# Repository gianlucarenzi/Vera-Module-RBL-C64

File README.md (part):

# VERA Module RBL-C64

<div align="center">

*🌐 English | [🌐 Italiano](#vera-module-rbl-c64-italiano)*

</div>

> [!WARNING]
> **v1.0 — PRE-PRODUCTION.**
> The PCB is routed and passes KiCad's DRC; the first boards are being made and are **not tested
> yet**. Firmware (ESP32, FPGA) and documentation have only been checked in simulation or on
> paper and may contain errors.

<div align="center">

**Commander X16 graphics and sound for the Commodore 64, through the expansion port.**

*▶ Teaser: 32 s with sound (Ctrl+click to open it in a new tab)*

</div>

## 🎮 What it can look like

What a game can look like on the VERA (320×240, 256 colours). These are **illustrative mock-ups
of two original demo games, not captures from the board**; `tools/make_demo_shots.py` draws them.

<div align="center">

*IRONHOLD (side-scrolling action) and CIRCUIT RUNNER (maze chase)*
</div>

## 📦 v1.0 — pre-production

- **USB:** CH340C USB-serial (internal clock, no crystal) on USB-C, with ESP32 auto-reset.
- **U11 WM8524** (C146242) is short at JLCPCB: it is in `jlcpcb-global-sourcing.txt`; choose
  **Global Sourcing** for that row when ordering.
- The BOM XML comes straight from the KiCad 5 schematic (`utilities/kicadcli`), which stops on
  parts without annotation; `./output_job.sh 1.0` makes the JLCPCB files.

---

<div style="background: #ffffff; border-radius: 16px; padding: 24px; margin: 24px 0; box-shadow: 0 4px 12px rgba(0,0,0,0.1); border: 1px solid #e0e0e0;">

## 📋 Table of Contents

- [🔍 Overview](#-overview)
- [✨ Features](#-features)
- [⚙️ Technical Specifications](#️-technical-specifications)
- [🔧 Hardware Components](#-hardware-components)
- [🖼️ Board Preview](#️-board-preview)
- [📐 PCB Layers](#-pcb-layers)
- [🔌 Connectors & Interfaces](#-connectors--interfaces)
- [⚡ Power Requirements](#-power-requirements)
- [🔨 Assembly Instructions](#-assembly-instructions)
- [📦 Bill of Materials](#-bill-of-materials)
- [💻 Programming & Configuration](#-programming--configuration)
- [📁 Project Structure](#-project-structure)
- [🤝 Contributing](#-contributing)
- [📄 License](#-license)

</div>

---

<div style="background: #ffffff; border-radius: 16px; padding: 24px; margin: 24px 0; box-shadow: 0 4px 12px rgba(0,0,0,0.1); border: 1px solid #e0e0e0;">

## 🔍 Overview

The **VERA Module RBL-C64** is an FPGA-based audio and video expansion card for the
**Commodore 64**. It plugs into the **expansion (cartridge) port** and adds, in the I/O
areas `IO1`/`IO2`, the VERA registers and a **256 KB GeoRAM** emulated by the ESP32.

### What is VERA?

**VERA** (Video Enhanced Retro Adapter) is originally designed for the 
Commander X16 computer, whose 65C02 bus is close to the 6510 one. It provides:

- **Advanced Graphics**: Multiple video layers, sprites, and high-resolution modes
- **Enhanced Audio**: Multi-channel digital audio with PCM and PSG capabilities  
- **Modern Connectivity**: VGA output, SD card storage, and USB programming
- **Retro Compatibility**: Integration with C64 software through a small register map

</div>

---

<div style="background: #ffffff; border-radius: 16px; padding: 24px; margin: 24px 0; box-shadow: 0 4px 12px rgba(0,0,0,0.1); border: 1px solid #e0e0e0;">

## ✨ Features

### 🎨 Graphics Capabilities

#### Video Output
- **VGA Output**: 640x480 @ 60Hz with analog RGB signals
- **Multiple Layers**: Background, foreground, and sprite layers
- **Color Depth**: 256 colors from a palette of 4096
- **Sprites**: Hardware-accelerated sprite engine
- **Scrolling**: Smooth horizontal and vertical scrolling

#### Audio Features
- **Digital Audio**: High-quality PCM audio output
- **Multi-channel**: Stereo audio
- **Audio Codec**: WM8524 for professional audio quality
- **3.5mm Jack**: Standard audio output connector

### 🔗 System Integration

#### Commodore 64 Compatibility
- **Expansion Port**: Direct connection to the C64 cartridge port, no ROM mapping (`/GAME`, `/EXROM` unused)
- **I/O Mapping**: VERA registers at `$DF00–$DF1F`, select latch at `$DFFD`, GeoRAM window at `$DE00–$DEFF` with page/block registers at `$DFFE`/`$DFFF`
- **GeoRAM 256 KB**: emulated in the ESP32 RAM, register compatible with the original cartridge
- **Bus Decoder**: cycles qualified by the C64 `/IO1` and `/IO2` lines (CPU accesses only, VIC-II fetches ignored); A0–A7 give the offset
- **Power Management**: Efficient 5V to 3.3V/1.2V conversion

#### Storage & Programming
- **SD Card Slot**: Micro SD for data storage and ROM loading
- **SPI Flash**: 16Mbit W25Q16 for FPGA configuration
- **USB Programming**: CH340C USB-to-serial on USB-C, with ESP32 auto-reset
- **SPI**: Direct FPGA programming interface

</div>

---

<div style="background: #ffffff; border-radius: 16px; padding: 24px; margin: 24px 0; box-shadow: 0 4px 12px rgba(0,0,0,0.1); border: 1px solid #e0e0e0;">

## ⚙️ Technical Specifications

### Core Specifications

| Component | Specification |
|-----------|---------------|
| **FPGA** | Lattice ICE40UP5K-SG48ITR |
| **Microcontroller** | ESP32-S3FN8 |
| **Flash Memory** | W25Q16JVSNIQ (16Mbit) |
| **Audio Codec** | WM8524CGEDT |
| **USB Interface** | CH340C (internal clock, no crystal) |
| **Power Regulators** | AMS1117-3.3V, AMS1117-1.2V, L7805 |
| **Crystal (VERA board)** | 25 MHz ECS-2033-250-BN (ICE40UP5K reference clock) |
| **Crystal (ESP32-S3)** | 40 MHz external — required; XTAL\_P (QFN56 pin 54) / XTAL\_N (pin 53) |
| **PCB Layers** | 4-layer (Signal/Power/GND/Signal) |
| **Board Size** | TBD mm x TBD mm |

### Electrical Characteristics

| Parameter | Min | Typ | Max | Unit |
|-----------|-----|-----|-----|------|
| **Supply Voltage** | 4.5 | 5.0 | 5.5 | V |
| **Current Consumption** | - | 800 | 1200 | mA |
| **Operating Temperature** | -10 | 25 | 70 | °C |
| **VGA Output Impedance** | - | 75 | - | Ω |
| **Audio Output Level** | - | 2.0 | - | Vrms |

</div>

---

<div style="background: #ffffff; border-radius: 16px; padding: 24px; margin: 24px 0; box-shadow: 0 4px 12px rgba(0,0,0,0.1); border: 1px solid #e0e0e0;">

## 🔧 Hardware Components

### Main Processing Units

#### FPGA - ICE40UP5K
- **Logic Elements**: 5,280 LUTs
- **Memory**: 120 Kbit BRAM, 1 Mbit SPRAM
- **I/O Pins**: 39 user I/O
- **Package**: QFN-48 (7x7mm)
- **Programming**: SPI configuration

#### ESP32-S3FN8
- **CPU**: Dual-core Xtensa LX7 @ 240 MHz
- **Memory**: 8 MB in-package Quad SPI flash, 512 KB SRAM
- **Connectivity**: Wi-Fi 802.11 b/g/n, Bluetooth 5 LE
- **GPIO**: 45 total (38 usable), all bidirectional
- **Package**: QFN-56 (7×7 mm)
- **Crystal**: requires an external **40 MHz crystal** on dedicated analog pins XTAL\_P (QFN56 pin 54) and XTAL\_N (pin 53) — mandatory for PLL startup; see PIN-MAPPING.md § 5
- **Role**: software 6510-bus controller — qualifies every cycle with `/IO1`/`/IO2`, reads A0–A7, R/W and D0–D7, drives `DEV_SEL_N` for the VERA registers and the data bus for GeoRAM reads; emulates the 256 KB GeoRAM in its internal RAM
- **Timing**: bus loop alone on Core 1 with interrupts masked (Core 0 prints the log on Serial); PHI2, R/W, `/IO1`, `/IO2` and `DEV_SEL_N` through **Dedicated GPIO** Xtensa TIE instructions (`ee.get_gpio_in` / `ee.wr_mask_gpio_out`, 1 CPU cycle) within the ~490 ns PHI2-high window of the ~1 MHz 6510 clock

### Interface Components

#### Audio System
- **Codec**: WM8524CGEDT (24-bit, 192kHz)
- **Interface**: From FPGA digital audio bus
- **Output**: 3.5mm stereo jack
- **SNR**: >100dB

#### Video System
- **Output**: 15-pin VGA connector
- **Resolution**: 640x480 @ 60Hz
- **Colors**: 8-bit RGB (256 colors)
- **Sync**: Separate H/V sync signals

</div>

---

<div style="background: #ffffff; border-radius: 16px; padding: 24px; margin: 24px 0; box-shadow: 0 4px 12px rgba(0,0,0,0.1); border: 1px solid #e0e0e0;">

## 🖼️ Board Preview

### 3D Renderings

#### Top View

*Top side showing main components and connectors*

#### Bottom View  

*Bottom side with additional components*

### Board Dimensions

- **Length**: TBD mm
- **Width**: TBD mm  
- **Thickness**: 1.6mm (4-layer PCB)
- **Mounting**: Commodore 64 expansion port (2×22 edge contacts, 2.54 mm pitch)
- **Connectors**: Flat for space efficiency. It needs a custom 3D printed case

</div>

---

<div style="background: #ffffff; border-radius: 16px; padding: 24px; margin: 24px 0; box-shadow: 0 4px 12px rgba(0,0,0,0.1); border: 1px solid #e0e0e0;">

## 📐 PCB Layers

### Layer Stack-up

#### Layer 1 - Top Copper (F.Cu)

*Component placement and signal routing*

#### Layer 2 - Power Plane (POWER)

*5V, 3.3V, and 1.2V power distribution*

#### Layer 3 - Ground Plane (GND)

*Solid ground plane for signal integrity*

#### Layer 4 - Bottom Copper (B.Cu)

*Additional signal routing and components*

</div>

---

<div style="background: #ffffff; border-radius: 16px; padding: 24px; margin: 24px 0; box-shadow: 0 4px 12px rgba(0,0,0,0.1); border: 1px solid #e0e0e0;">

## 🔌 Connectors & Interfaces

### External Connections

#### Commodore 64 Expansion Port
- **Connector**: expansion (cartridge) port, 2×22 edge contacts, 2.54 mm pitch
- **Address Range**: `IO1` $DE00–$DEFF, `IO2` $DF00–$DFFF
- **Signals used**: D0–D7, A0–A15, PHI2, R/W, `/IO1`, `/IO2`, `/RESET`, `/IRQ`; `BA` and `/DMA` only to test points
- **Unused lines**: `/GAME`, `/EXROM`, `/ROML`, `/ROMH`, `/NMI`, Dot Clock — left unconnected
- **Outputs**: `/IRQ` and `/RESET` through the open-drain buffers `U26` and `U27` (SN74LVC1G07): the board only pulls the shared lines low
- **No audio input** on the expansion port: the VERA audio mix is on test point `TP5`

#### Video Output (J2)
| Pin | Signal | Description |
|-----|--------|-------------|
| 1-3 | RGB | Red, Green, Blue analog signals |
| 13-14 | H/V Sync | Horizontal/Vertical sync |
| 6-10 | GND | Ground connections |
| 11-12 | Audio L/R | Stereo audio output |

#### Storage Interfaces
- **SD Card Slot (J3)**: Micro SD card interface
- **SPI Flash**: On-board 16Mbit storage
- **USB Port (J4)**: Programming and data transfer

### Programming Interfaces

#### ICEPROG Connector (J6)
| Pin | Signal | Function |
|-----|--------|----------|
| 1 | 5V | Power supply |
| 2 | FPGA_CDONE/PULL-UP | FPGA Programmed |
| 3 | FPGA_RESET | FPGA Reset |
| 4 | MISO | SPI data in |
| 5 | MOSI | SPI data out |
| 6 | SCK | SPI clock |
| 7 | SS | SPI select |
| 8 | GND | Ground |

#### Reset & Control
- **Reset Button (SW1)**: ESP32 system reset
- **DIP Switch (SW2)**: Configuration options
- **Status LEDs**: Power, programming, activity indicators

</div>

---

<div style="background: #ffffff; border-radius: 16px; padding: 24px; margin: 24px 0; box-shadow: 0 4px 12px rgba(0,0,0,0.1); border: 1px solid #e0e0e0;">

## ⚡ Power Requirements

### Power Distribution

#### Power Rails
| Rail | Voltage | Current | Components |
|------|---------|---------|------------|
| **5V** | 5.0V ± 5% | 200mA | Input from the C64 expansion port, USB |
| **3.3V** | 3.3V ± 3% | 400mA | ESP32, logic, interfaces |
| **1.2V** | 1.2V ± 3% | 300mA | FPGA core voltage |

#### Power Sources
1. **C64 expansion port**: Primary 5V supply from the computer (shared with the C64: check the board consumption against the power supply budget)
2. **USB**: Alternative 5V for programming/testing
3. **External**: Optional external 5V supply (J5)

#### Power Protection
- **Ideal diodes** (`U17`, `U18` MAX40200) on the jack and USB inputs; **no diode on the C64 5 V**: program the board and use USB/jack only with the board out of the C64 (`VERA-C64-HW-REQUIREMENTS.md` §2.11)
- **Ferrite Beads**: EMI filtering
- **Decoupling**: Extensive capacitor network
- **Current Limiting**: Overcurrent protection

</div>

---

<div style="background: #ffffff; border-radius: 16px; padding: 24px; margin: 24px 0; box-shadow: 0 4px 12px rgba(0,0,0,0.1); border: 1px solid #e0e0e0;">

## 🔨 Assembly Instructions

### Component Assembly

#### Assembly Order
1. **SMD Components**: Start with smallest components (0603, 0805)
2. **ICs**: Place all integrated circuits
3. **Connectors**: Install all external connectors
4. **Through-hole**: Add any remaining THT components
5. **Testing**: Verify power rails before first power-on

#### Special Considerations
- **FPGA**: Use proper ESD precautions
- **BGA Components**: Requires professional assembly
- **Thermal Management**: Ensure adequate cooling
- **Impedance Control**: Maintain 50Ω for high-speed signals

### Testing & Validation

#### Power-On Tests
1. **Visual Inspection**: Check for shorts, proper orientation
2. **Power Rails**: Verify all voltages within tolerance
3. **Clock Signals**: Confirm oscillator operation
4. **Communication**: Test SPI, I2C, UART interfaces

#### Functional Tests
1. **FPGA Programming**: Load test bitstream
2. **Video Output**: Verify VGA signal generation
3. **Audio Output**: Test audio codec functionality
4. **C64 Interface**: Confirm the select latch ($DFFD), the VERA registers ($DF00–$DF1F) and GeoRAM read/write ($DE00, $DFFE/$DFFF)

</div>

---

<div style="background: #ffffff; border-radius: 16px; padding: 24px; margin: 24px 0; box-shadow: 0 4px 12px rgba(0,0,0,0.1); border: 1px solid #e0e0e0;">

## 📦 Bill of Materials

### Component Categories

#### Major Components
- **1x** ICE40UP5K-SG48ITR FPGA
- **1x** ESP32-S3FN8 Microcontroller  
- **1x** W25Q16JVSNIQ SPI Flash
- **1x** WM8524CGEDT Audio Codec
- **1x** CH340C USB Interface

#### Passive Components
- **23x** 1µF Capacitors (1206)
- **20x** 100nF Capacitors (1206)
- **6x** 10µF Capacitors (1206)
- **Various** Resistors (0805/1206)
- **1x** 25 MHz Crystal Oscillator (VERA board — ICE40UP5K reference clock)
- **1x** 40 MHz Crystal + 2×10 pF load capacitors (ESP32-S3 — mandatory)

#### Connectors
- **1x** 15-pin VGA Connector
- **1x** Micro SD Card Slot
- **1x** USB Type-C Connector
- **1x** 3.5mm Audio Jack
- **1x** 8-pin Programming Header

### Cost Analysis

| Category | Estimated Cost | Percentage |
|----------|----------------|------------|
| **FPGA** | $15-20 | 35% |
| **ESP32** | $8-12 | 20% |
| **Connectors** | $5-8 | 15% |
| **Passives** | $3-5 | 10% |
| **PCB** | $8-12 | 20% |
| **Total** | **$39-57** | **100%** |

*Costs are estimates for small quantity production*

</div>

---

<div style="background: #ffffff; border-radius: 16px; padding: 24px; margin: 24px 0; box-shadow: 0 4px 12px rgba(0,0,0,0.1); border: 1px solid #e0e0e0;">

## 💻 Programming & Configuration

### FPGA Programming

#### Programming Methods
1. **iceprog** with an FTDI FT232H / FT2232H adapter on J6 (steps below)
2. **openFPGALoader**, same wiring

#### Programming Steps (iceprog, through J6)

<div align="center">

</div>

The VERA bitstream lives in the SPI flash U10 (W25Q16); the FPGA loads it at power-up.
`iceprog` writes it through **J6** with an FTDI FT232H or FT2232H adapter (MPSSE):

| J6 pin | Signal | FT232H / FT2232H (channel A) |
|---|---|---|
| 1 | 5 V (JP1) or 3.3 V (JP3), solder jumper | not needed: leave it unconnected |
| 2 | CDONE | ADBUS6 |
| 3 | CRESET | ADBUS7 |
| 4 | MISO (flash DO) | ADBUS2 |
| 5 | MOSI (flash DI) | ADBUS1 |
| 6 | SCK | ADBUS0 |
| 7 | SS (flash /CS) | ADBUS4 |
| 8 | GND | GND |

1. Power the board (in the computer) and **stop the ESP32**: hold BOOT0 (SW3), press and release
   RESET (SW1), release BOOT0. In download mode its pins are inputs; running, the firmware drives
   CRESET (GPIO 38) high against iceprog.
2. **Close JP2** ("FPGA PROGRAMMING"): CDONE goes to GND, so U9 selects the flash and U8 takes
   the microSD off the SPI bus.
3. Write and verify the flash:
   ```bash
   sudo apt install fpga-icestorm      # iceprog
   iceprog -t                          # reads the flash ID (W25Q16: ef 40 15)
   iceprog vera_module.bin             # erase, write, verify (the bitstream is not provided)
   iceprog -c vera_module.bin          # verify only
   ```
   With JP2 closed iceprog reports `cdone: low`: that is expected.
4. **Open JP2** and press RESET (SW1): the ESP32 firmware pulses CRESET, the FPGA loads the new
   bitstream and CDONE goes high (the "VERA READY" LED lights up).

#### Development Tools
- **IceStorm**: Open-source FPGA toolchain
- **Yosys**: Verilog synthesis
- **NextPNR**: Place and route
- **KiCad**: PCB design and layout

### ESP32 Configuration

#### ESP32 Firmware
The ESP32-S3FN8 handles:
- **Core split**: the bus loop (`MonitorTask`) runs alone on **Core 1** with interrupts masked and never yields; **Core 0** runs `LogTask`, which prints on Serial the events passed through a lock-free ring buffer
- **Startup sync**: ARESET and CRESET asserted LOW immediately in `setup()`. `setup()` enables the address translators (`ABUS_OE_N`, GPIO 47, after the strapping pins are latched), releases CRESET, polls CDONE until the ICE40UP5K bitstream is loaded (< 100 ms typical, 5 s timeout) and waits for the VERA power-on reset; `MonitorTask` then releases ARESET — the C64 starts with bus and FPGA already ready
- **Cycle qualification**: after the PHI2 rising edge the loop waits, for at most `IO_QUALIFY_NS` (200 ns), for `/IO1` or `/IO2`; other cycles, including VIC-II fetches, are skipped untouched
- **Critical path in inline assembly**: once `/IOx` is seen, 5 instructions + 1 APB read to `DEV_SEL_N`, ~10 instructions to the GeoRAM byte on the bus (two posted stores); IO2 decoded by a table in `include/bus_decode.h`, checked by a host test
- **GeoRAM**: 256 KB in ordinary DRAM `.bss`; D0–D7 driven via `GPIO.out` for reads of the `$DE00` window, from a pointer to the current page updated only on `$DFFE`/`$DFFF` writes
- **Writes**: the 6510 data is sampled `BUS_WR_SAMPLE_NS` (300 ns) after PHI2 rises; side effects are applied in the rest of PHI2
- **Debugging**: UART0 on GPIO43 (TX) / GPIO44 (RX), 115200 baud

I/O map (single build, `esp32s3fn8`):

| Address | Access | Function | Responds |
|---------|--------|----------|----------|
| `$DE00–$DEFF` | R/W | GeoRAM window (256-byte page) | ESP32 |
| `$DF00–$DF1F` | R/W | VERA registers | FPGA, `DEV_SEL_N` asserted |
| `$DFFD` | W | VERA select latch: non-zero selects, `0` deselects | ESP32 (snoop) |
| `$DFFE` | W | GeoRAM page register (0–63) | ESP32 (snoop) |
| `$DFFF` | W | GeoRAM block register (0–15) | ESP32 (snoop) |

The VERA responds **only while selected** through `$DFFD`; the GeoRAM (window and
registers) is **always active**, like the original cartridge, so existing GeoRAM software
works without touching `$DFFD`.
GeoRAM offset = block × 16384 + page × 256 + (addr & $FF). The registers are write-only,
cleared at power-on and kept across a C64 reset, like the original cartridge. They are
decoded exactly at `$DFFE`/`$DFFF` (no `$DF80–$DFFD` mirrors), so the latch at `$DFFD`
does not collide with them.

```
LDA #$04 : STA $DFFF   ; GeoRAM block 4 (always active)
LDA #$23 : STA $DFFE   ; GeoRAM page 35
LDA $DE45              ; GeoRAM byte $12345
LDA #$01 : STA $DFFD   ; select the VERA at $DF00-$DF1F
LDA #$00 : STA $DFFD   ; deselect the VERA
```

Details, timing analysis and critical-path figures: [`firmware/MCU/README.md`](firmware/MCU/README.md)
and `firmware/MCU/Vera_Module_Analisys.ITA.pdf`.

#### Programming ESP32
The firmware is built with **PlatformIO** (install via `pip install platformio`):
```bash
# Build firmware
cd firmware/MCU
pio run -e esp32s3fn8

# Flash firmware — through the USB-C port (on-board CH340C on UART0, GPIO 43/44)
pio run -e esp32s3fn8 --target upload
```

> **Note**: USB CDC is disabled because GPIO 19 (USB D−) and GPIO 20 (USB D+) are reused
> as address lines A7 and A8. The on-board CH340C (USB-C) is wired to UART0 (GPIO 43/44)
> and resets the ESP32 into the bootloader through DTR/RTS: no external adapter is needed.

</div>

---

<div style="background: #ffffff; border-radius: 16px; padding: 24px; margin: 24px 0; box-shadow: 0 4px 12px rgba(0,0,0,0.1); border: 1px solid #e0e0e0;">

## 📁 Project Structure

The design workflow, from the schematic to the JLCPCB order (stock check, library update, ERC, netlist, PCB and net classes, DRC, `output_job.sh`, files to send), is described in [WORKFLOW.md](WORKFLOW.md) (in Italian, also as [PDF](WORKFLOW.pdf)).

### Repository Organization

```
Vera-Module-RBL-C64/
├── 📄 README.md                    # This documentation
├── 📄 WORKFLOW.md                  # Design workflow, schematic to JLCPCB order
├── 📄 PIN-MAPPING.md               # ESP32-S3 / level-shifter pin mapping, C64 port (§ 9)
├── 📄 VERA-C64-HW-REQUIREMENTS.md # VERA bus requirements & bring-up plan
├── 📄 LICENSE                      # GPL v3 license
├── 📁 firmware/
│   ├── 📁 MCU/                     # ESP32-S3 firmware (PlatformIO), analysis document
│   └── 📁 FPGA/                    # iCE40UP5K bus interface (C6502_Interface.vhd)
├── ⚙️ VERA-MODULE-RBL.pro         # KiCad project file
├── 📄 VERA-MODULE-RBL.sch         # Main schematic
├── 🔧 VERA-MODULE-RBL.kicad_pcb   # PCB layout
├── 📄 VERA-MODULE-RBL.csv         # Bill of materials
├── 🐍 jlcpcb-check-bom.py        # BOM processing script
├── 📁 images/                      # Board images and renders
│   ├── 🖼️ VERA-MODULE-RBL-TOP.png
│   ├── 🖼️ VERA-MODULE-RBL-BOTTOM.png
│   ├── 🖼️ F.Cu-L1.png            # PCB layer images
│   ├── 🖼️ POWER-L2.png
│   ├── 🖼️ GND-L3.png
│   └── 🖼️ B.Cu-L4.png
├── 📁 production/                  # Manufacturing files
│   ├── 📄 *.gbl, *.gtl            # Gerber files
│   ├── 📄 *.drl                   # Drill files
│   └── 📄 *.gbrjob                # Job files
├── 📁 ibom/                       # Interactive BOM
│   └── 🌐 ibom.html
└── 📁 schematics/                 # Individual schematics
    ├── 📄 vera-fpga.sch           # FPGA module
    ├── 📄 busdecoder.sch          # Bus decoder
    ├── 📄 cartridgeInterface.sch   # Cartridge interface
    ├── 📄 vera-fpga-flash.sch     # Flash memory
    └── 📄 powersupply.sch         # Power management
```

### Hardware notes (read before bring-up)

- [`PIN-MAPPING.md` § 9](PIN-MAPPING.md#9-porta-di-espansione-scelte-hardware) —
  hardware of the expansion port: connector, `/IO1`/`/IO2` inputs on GPIO 41/42 through
  `U6`, `U19` output-enable gating with `DEV_SEL_N` and `/IO1`, open-drain `/IRQ` and `/RESET`.
- [`VERA-C64-HW-REQUIREMENTS.md`](VERA-C64-HW-REQUIREMENTS.md) — what the VERA FPGA
  requires from the bus (separate RD/WR, write data hold, read side effects, reconfiguration),
  plus the bring-up test plan.

### Design Files

#### KiCad Files
- **Schematic**: Multi-sheet hierarchical design
- **PCB Layout**: 4-layer board with controlled impedance
- **3D Models**: Custom component models
- **Footprints**: Custom connector footprints

#### Manufacturing Files
- **Gerber Files**: Industry-standard PCB fabrication
- **Drill Files**: NC drill and via specifications  
- **Pick & Place**: SMT assembly coordinates
- **BOM**: Component specifications with LCSC part numbers

</div>

---

<div style="background: #ffffff; border-radius: 16px; padding: 24px; margin: 24px 0; box-shadow: 0 4px 12px rgba(0,0,0,0.1); border: 1px solid #e0e0e0;">

## 🤝 Contributing

### Development Guidelines

#### Contributing Process
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
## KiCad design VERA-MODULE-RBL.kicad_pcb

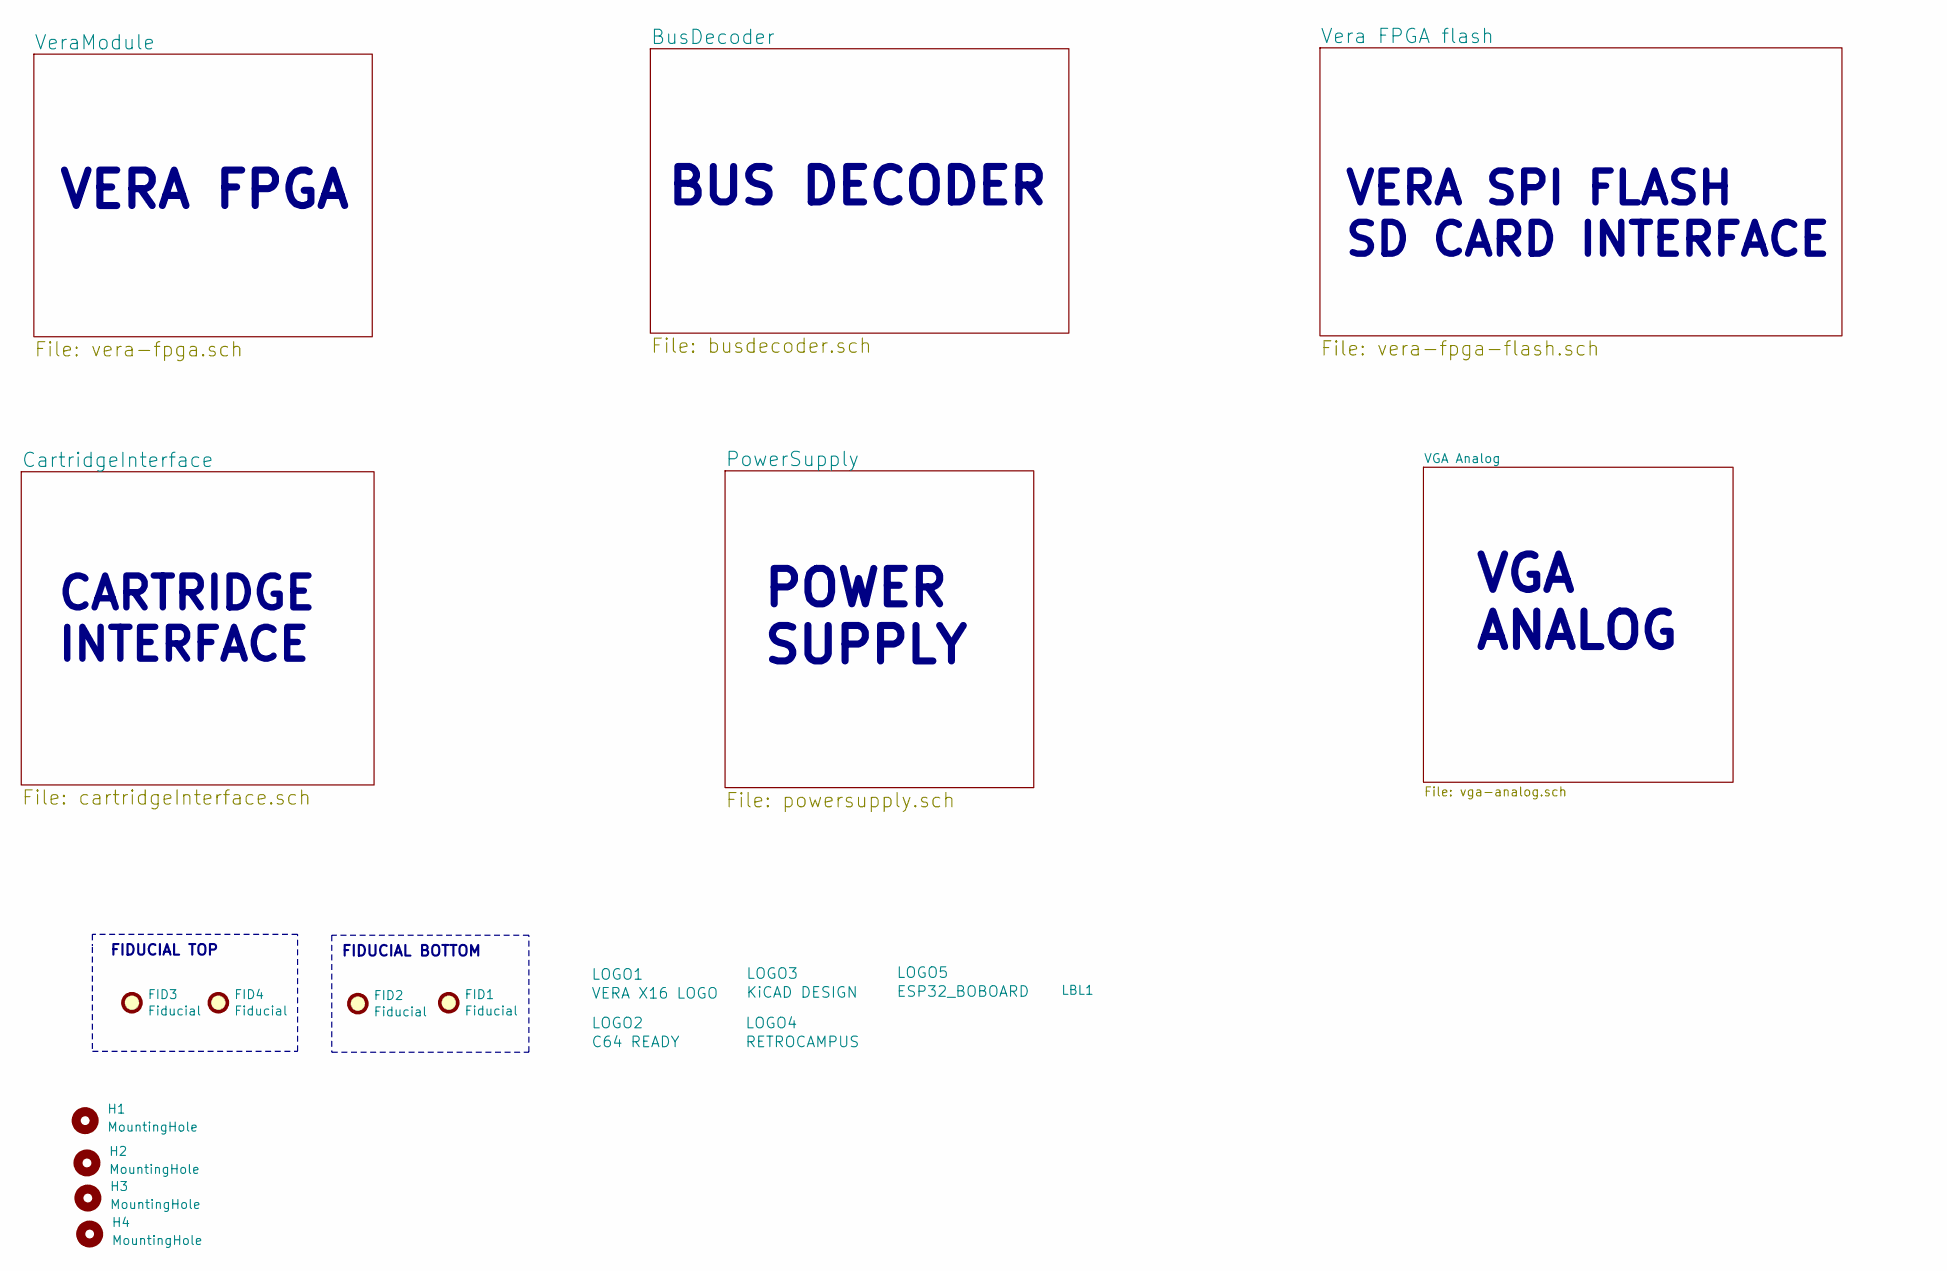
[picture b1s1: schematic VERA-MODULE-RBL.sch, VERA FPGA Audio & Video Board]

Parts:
FID1, FID2, FID3, FID4: Fiducial; Fiducial_0.5mm_Mask1mm
H1, H2, H3, H4: MountingHole; MountingHole_3.2mm_M3
LBL1: Label-20mmx10mm; Label-20mmx10mm-Silkscreen
LOGO1: VERA X16 LOGO; x16logo
LOGO2: C64 READY; c64_ready_8mm_REV
LOGO3: KiCAD DESIGN; KiCad-Logo2_6mm_SilkScreen
LOGO4: RETROCAMPUS; retrocampus_silkscreen_16.9mm_8.3mm
LOGO5: ESP32_BOBOARD; ESP32_BOBOARD_5V_21.7mmx21.7mm

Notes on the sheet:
VERA FPGA
BUS DECODER
CARTRIDGE INTERFACE
VERA SPI FLASH SD CARD INTERFACE
POWER SUPPLY
FIDUCIAL TOP
FIDUCIAL BOTTOM
VGA ANALOG

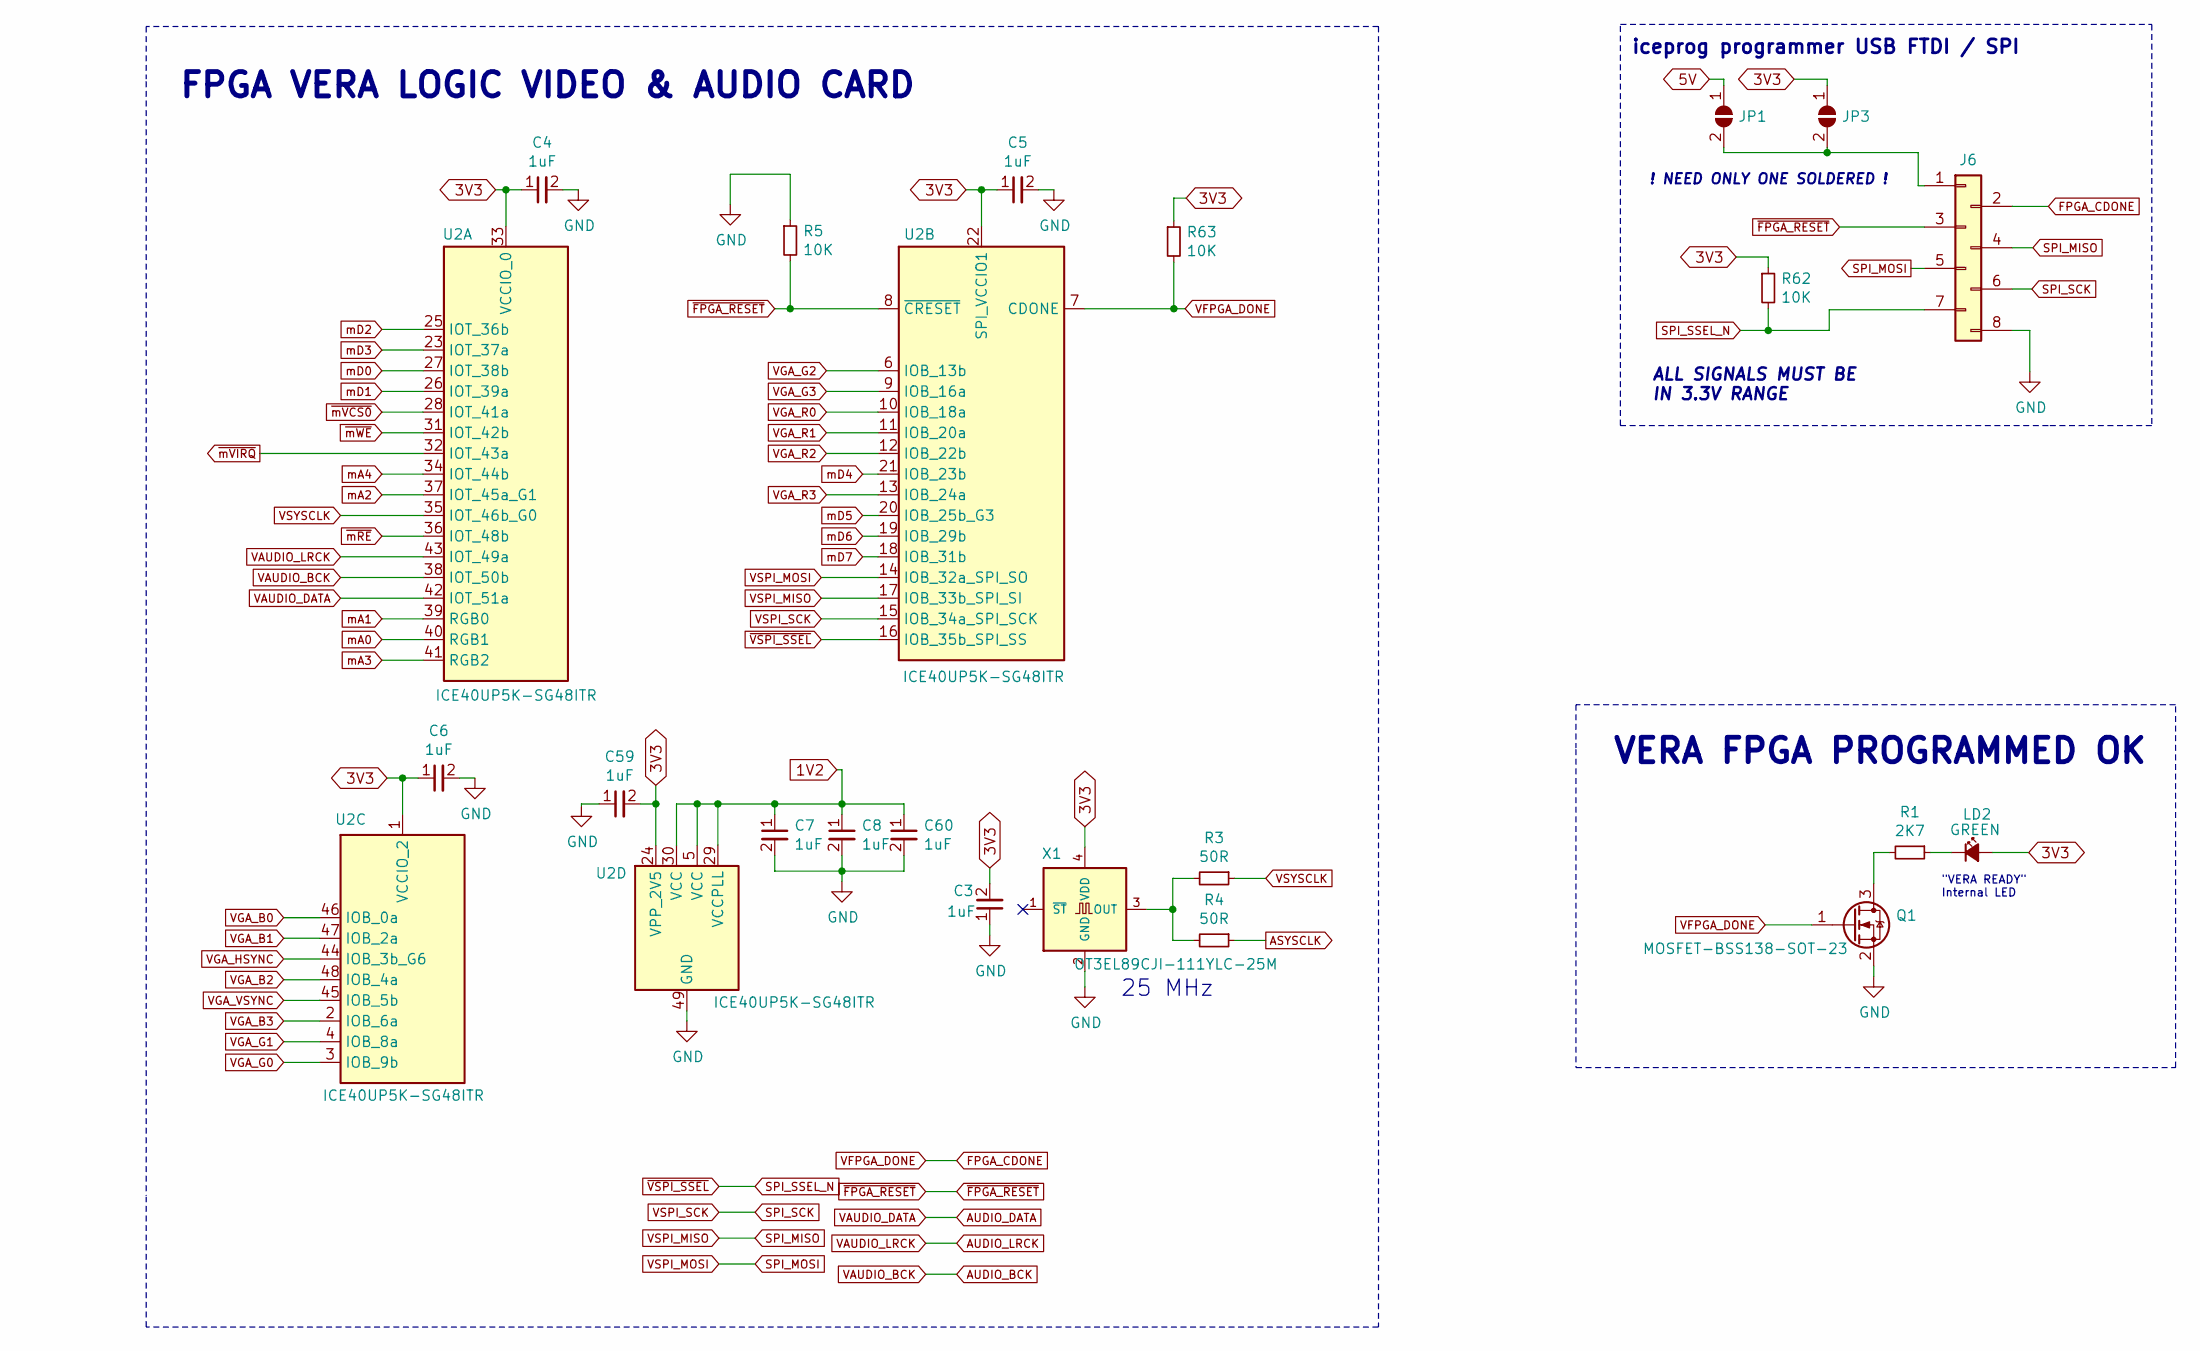
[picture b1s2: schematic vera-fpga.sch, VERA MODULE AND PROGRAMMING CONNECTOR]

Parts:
C3, C4, C5, C6, C7, C8, C59, C60: 1uF; C_0805_2012Metric_Pad1.18x1.45mm_HandSolder; LCSC C28323
J6: CONN_SMD_01x08_Staggered_2.54mm; PinSocket_1x08_P2.54mm_Vertical_SMD_Pin1Right; LCSC C42380985
JP1, JP3: SolderJumper_2_Open; SolderJumper-2_P1.3mm_Open_RoundedPad1.0x1.5mm
LD2: GREEN; LED_0805_2012Metric_Pad1.15x1.40mm_HandSolder; LCSC C2297
Q1: MOSFET-BSS138-SOT-23; SOT-23; LCSC C7420339
R1: 2K7; R_0805_2012Metric_Pad1.20x1.40mm_HandSolder; LCSC C17530
R3, R4: 50R; R_0805_2012Metric_Pad1.20x1.40mm_HandSolder; LCSC C2828866
R5, R62, R63: 10K; R_0805_2012Metric_Pad1.20x1.40mm_HandSolder; LCSC C17414
U2: ICE40UP5K-SG48ITR; QFN-48-1EP_7x7mm_P0.5mm_EP5.6x5.6mm; LCSC C2678152
X1: OT3EL89CJI-111YLC-25M; OSC_ECS-2033-250-BN; LCSC C7471623

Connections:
1V2: C7.1, C8.1, C60.1, U2.5 (VCC), U2.29 (VCCPLL), U2.30 (VCC); also elsewhere on the board
3V3: C3.2, C4.1, C5.1, C6.1, C59.2, JP3.1 (A), LD2.2 (A), R62.1, R63.1, U2.1 (VCCIO_2), U2.22 (SPI_VCCIO1), U2.24 (VPP_2V5), U2.33 (VCCIO_0), X1.4 (VDD); also elsewhere on the board
5V: JP1.1 (A); also elsewhere on the board
ASYSCLK: R4.1; also elsewhere on the board
AUDIO_BCK: U2.38 (IOT_50b); also elsewhere on the board
AUDIO_DATA: U2.42 (IOT_51a); also elsewhere on the board
AUDIO_LRCK: U2.43 (IOT_49a); also elsewhere on the board
FPGA_CDONE: J6.2, Q1.1 (G), R63.2, U2.7 (CDONE); also elsewhere on the board
GND: C3.1, C4.2, C5.2, C6.2, C7.2, C8.2, C59.1, C60.2, J6.8, Q1.2 (S), R5.1, U2.49 (GND), X1.2 (GND); also elsewhere on the board
unnamed: J6.1, JP1.2 (B), JP3.2 (B)
unnamed: LD2.1 (K), R1.1
unnamed: Q1.3 (D), R1.2
unnamed: R3.2, R4.2, X1.3 (OUT)
SPI_MISO: J6.4, U2.17 (IOB_33b_SPI_SI); also elsewhere on the board
SPI_MOSI: J6.5, U2.14 (IOB_32a_SPI_SO); also elsewhere on the board
SPI_SCK: J6.6, U2.15 (IOB_34a_SPI_SCK); also elsewhere on the board
SPI_SSEL_N: J6.7, R62.2, U2.16 (IOB_35b_SPI_SS); also elsewhere on the board
VGA_B0: U2.46 (IOB_0a); also elsewhere on the board
VGA_B1: U2.47 (IOB_2a); also elsewhere on the board
VGA_B2: U2.48 (IOB_4a); also elsewhere on the board
VGA_B3: U2.2 (IOB_6a); also elsewhere on the board
VGA_G0: U2.3 (IOB_9b); also elsewhere on the board
VGA_G1: U2.4 (IOB_8a); also elsewhere on the board
VGA_G2: U2.6 (IOB_13b); also elsewhere on the board
VGA_G3: U2.9 (IOB_16a); also elsewhere on the board
VGA_HSYNC: U2.44 (IOB_3b_G6); also elsewhere on the board
VGA_R0: U2.10 (IOB_18a); also elsewhere on the board
VGA_R1: U2.11 (IOB_20a); also elsewhere on the board
VGA_R2: U2.12 (IOB_22b); also elsewhere on the board
VGA_R3: U2.13 (IOB_24a); also elsewhere on the board
VGA_VSYNC: U2.45 (IOB_5b); also elsewhere on the board
VSYSCLK: R3.1, U2.35 (IOT_46b_G0)
mA0: U2.40 (RGB1); also elsewhere on the board
mA1: U2.39 (RGB0); also elsewhere on the board
mA2: U2.37 (IOT_45a_G1); also elsewhere on the board
mA3: U2.41 (RGB2); also elsewhere on the board
mA4: U2.34 (IOT_44b); also elsewhere on the board
mD0: U2.27 (IOT_38b); also elsewhere on the board
mD1: U2.26 (IOT_39a); also elsewhere on the board
mD2: U2.25 (IOT_36b); also elsewhere on the board
mD3: U2.23 (IOT_37a); also elsewhere on the board
mD4: U2.21 (IOB_23b); also elsewhere on the board
mD5: U2.20 (IOB_25b_G3); also elsewhere on the board
mD6: U2.19 (IOB_29b); also elsewhere on the board
mD7: U2.18 (IOB_31b); also elsewhere on the board
~FPGA_RESET: J6.3, R5.2, U2.8 (~CRESET); also elsewhere on the board
~mRE: U2.36 (IOT_48b); also elsewhere on the board
~mVCS0: U2.28 (IOT_41a); also elsewhere on the board
~mVIRQ: U2.32 (IOT_43a); also elsewhere on the board
~mWE: U2.31 (IOT_42b); also elsewhere on the board

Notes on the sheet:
"VERA READY" Internal LED
25 MHz
FPGA VERA LOGIC VIDEO & AUDIO CARD
VERA FPGA PROGRAMMED OK
iceprog programmer USB FTDI / SPI
ALL SIGNALS MUST BE IN 3.3V RANGE
! NEED ONLY ONE SOLDERED !

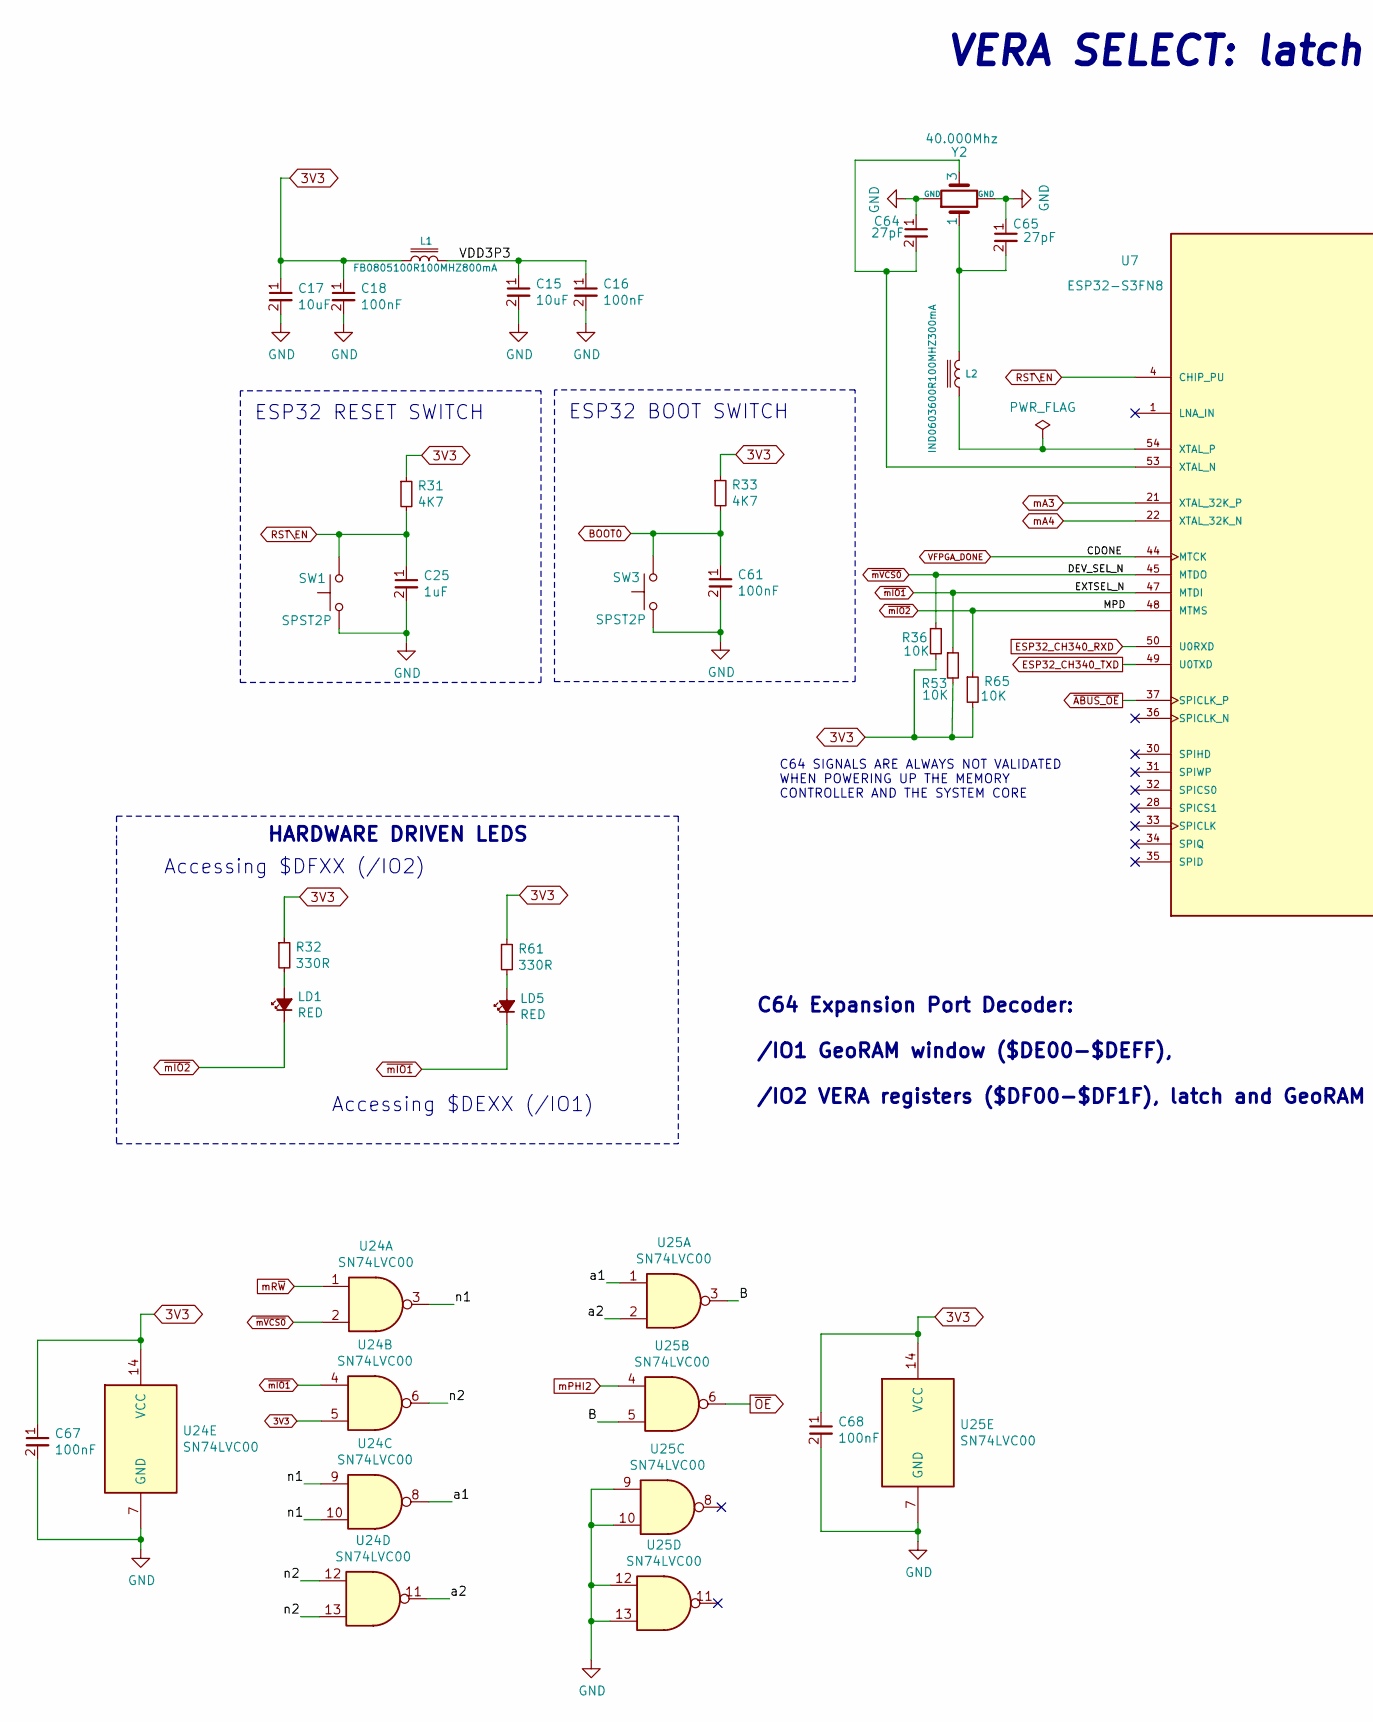
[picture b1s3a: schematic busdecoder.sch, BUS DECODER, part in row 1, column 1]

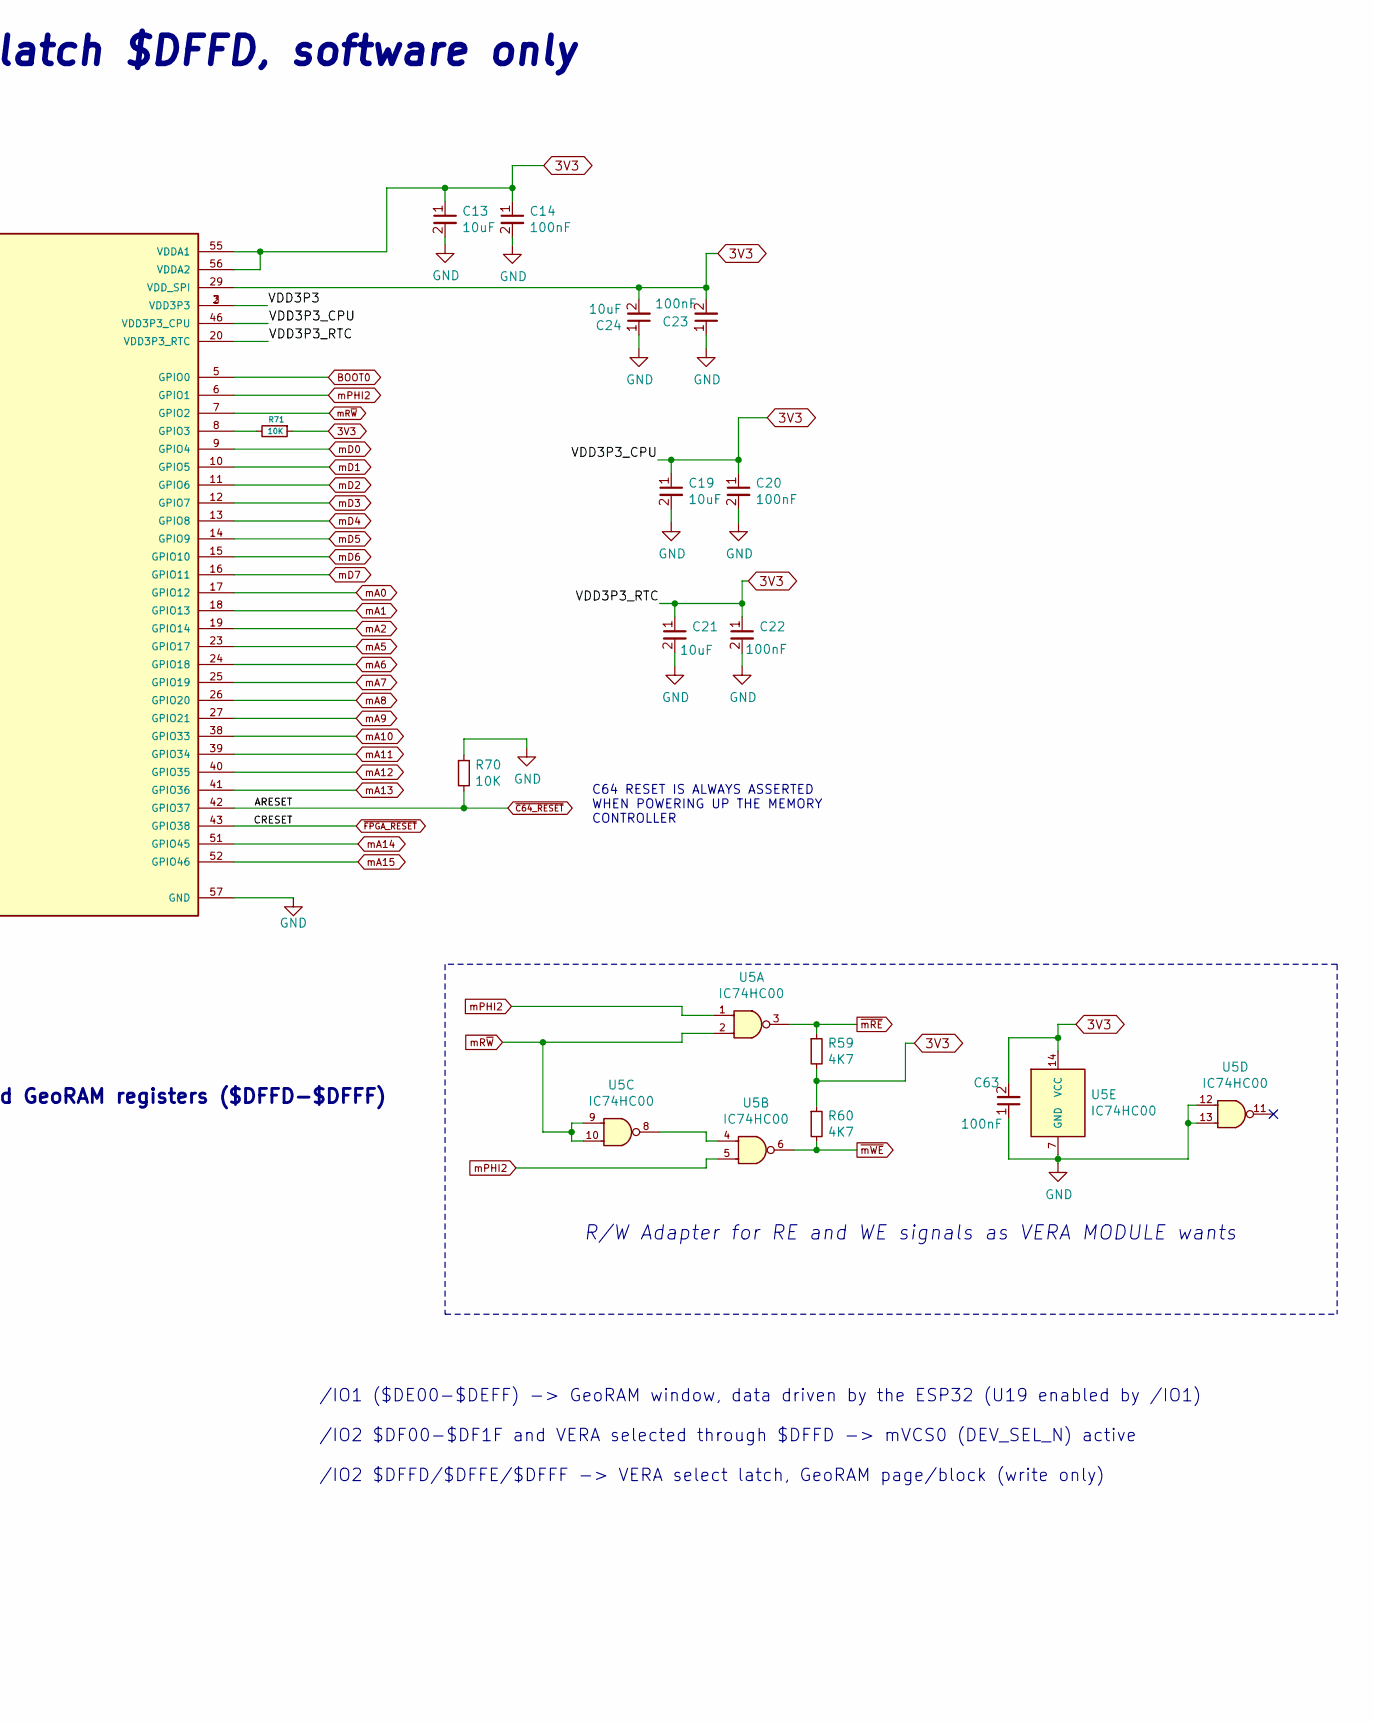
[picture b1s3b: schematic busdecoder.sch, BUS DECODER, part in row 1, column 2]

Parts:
C13, C15, C17, C19, C21, C24: 10uF; C_0805_2012Metric_Pad1.18x1.45mm_HandSolder; LCSC C440198
C14, C16, C18, C20, C22, C23, C61, C63, C67, C68: 100nF; C_0805_2012Metric_Pad1.18x1.45mm_HandSolder; LCSC C28233
C25: 1uF; C_0805_2012Metric_Pad1.18x1.45mm_HandSolder; LCSC C28323
C64, C65: 27pF; C_0805_2012Metric_Pad1.18x1.45mm_HandSolder; LCSC C1808
L1: FB0805100R100MHZ800mA; L_0805_2012Metric_Pad1.15x1.40mm_HandSolder; LCSC C1015
L2: IND0603600R100MHZ300mA; L_0603_1608Metric_Pad1.05x0.95mm_HandSolder; LCSC C139271
LD1, LD5: RED; LED_1206_3216Metric_Pad1.42x1.75mm_HandSolder; LCSC C965822
R31, R33, R59, R60: 4K7; R_0805_2012Metric_Pad1.20x1.40mm_HandSolder; LCSC C17673
R32, R61: 330R; R_0805_2012Metric_Pad1.20x1.40mm_HandSolder; LCSC C17630
R36, R53, R65, R70, R71: 10K; R_0805_2012Metric_Pad1.20x1.40mm_HandSolder; LCSC C17414
SW1, SW3: SPST2P; SPST-7.3x3.9x2.5-WUERTH-434121025816; LCSC C318911
U5: IC74HC00; SOIC-14_3.9x8.7mm_P1.27mm; LCSC C5586
U7: ESP32-S3FN8; IC_ESP32-S3FN8-QFN40P700X700X90-57N; Manufacturer PN ESP32-S3FN8; LCSC C2913196
U24, U25: SN74LVC00; TSSOP-14_4.4x5mm_P0.65mm; LCSC C7803
Y2: 40.000Mhz; Crystal_SMD_2520-4Pin_2.5x2.0mm; LCSC C284176

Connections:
3V3: C13.1, C14.1, C17.1, C18.1, C19.1, C20.1, C21.1, C22.1, C23.2, C24.2, C63.2, C67.1, C68.1, L1.1, R31.1, R32.1, R33.1, R36.2, R53.2, R59.2, R60.1, R61.1, R65.2, R71.1, U5.14 (VCC), U7.20 (VDD3P3_RTC), U7.29 (VDD_SPI), U7.46 (VDD3P3_CPU), U7.55 (VDDA1), U7.56 (VDDA2), U24.5, U24.14 (VCC), U25.14 (VCC); also elsewhere on the board
/BusDecoder/B: U25.3, U25.5
/BusDecoder/VDD3P3: C15.1, C16.1, L1.2, U7.2 (VDD3P3), U7.3 (VDD3P3)
/BusDecoder/a1: U24.8, U25.1
/BusDecoder/a2: U24.11, U25.2
/BusDecoder/n1: U24.3, U24.9, U24.10
/BusDecoder/n2: U24.6, U24.12, U24.13
BOOT0: C61.1, R33.2, SW3.2, U7.5 (GPIO0); also elsewhere on the board
ESP32_CH340_RXD: U7.50 (U0RXD); also elsewhere on the board
ESP32_CH340_TXD: U7.49 (U0TXD); also elsewhere on the board
FPGA_CDONE: U7.44 (MTCK); also elsewhere on the board
GND: C13.2, C14.2, C15.2, C16.2, C17.2, C18.2, C19.2, C20.2, C21.2, C22.2, C23.1, C24.1, C25.2, C61.2, C63.1, C64.1, C65.1, C67.2, C68.2, R70.1, SW1.1, SW3.1, U5.7 (GND), U5.12 (4A), U5.13 (4B), U7.57 (GND), U24.7 (GND), U25.7 (GND), U25.9, U25.10, U25.12, U25.13, Y2.2 (GND), Y2.4 (GND); also elsewhere on the board
unnamed: C64.2, U7.53 (XTAL_N), Y2.3
unnamed: C65.2, L2.2, Y2.1
unnamed: L2.1, U7.54 (XTAL_P)
unnamed: LD1.2 (A), R32.2
unnamed: LD5.2 (A), R61.2
unnamed: R71.2, U7.8 (GPIO3)
unnamed: U5.4 (4A), U5.8 (4Y)
RST\EN: C25.1, R31.2, SW1.2, U7.4 (CHIP_PU); also elsewhere on the board
mA0: U7.17 (GPIO12); also elsewhere on the board
mA1: U7.18 (GPIO13); also elsewhere on the board
mA2: U7.19 (GPIO14); also elsewhere on the board
mA3: U7.21 (XTAL_32K_P); also elsewhere on the board
mA4: U7.22 (XTAL_32K_N); also elsewhere on the board
mA5: U7.23 (GPIO17); also elsewhere on the board
mA6: U7.24 (GPIO18); also elsewhere on the board
mA7: U7.25 (GPIO19); also elsewhere on the board
mA8: U7.26 (GPIO20); also elsewhere on the board
mA9: U7.27 (GPIO21); also elsewhere on the board
mA10: U7.38 (GPIO33); also elsewhere on the board
mA11: U7.39 (GPIO34); also elsewhere on the board
mA12: U7.40 (GPIO35); also elsewhere on the board
mA13: U7.41 (GPIO36); also elsewhere on the board
mA14: U7.51 (GPIO45); also elsewhere on the board
mA15: U7.52 (GPIO46); also elsewhere on the board
mD0: U7.9 (GPIO4); also elsewhere on the board
mD1: U7.10 (GPIO5); also elsewhere on the board
mD2: U7.11 (GPIO6); also elsewhere on the board
mD3: U7.12 (GPIO7); also elsewhere on the board
mD4: U7.13 (GPIO8); also elsewhere on the board
mD5: U7.14 (GPIO9); also elsewhere on the board
mD6: U7.15 (GPIO10); also elsewhere on the board
mD7: U7.16 (GPIO11); also elsewhere on the board
mPHI2: U5.1 (4A), U5.5 (4B), U7.6 (GPIO1), U25.4; also elsewhere on the board
mR~W: U5.2 (4B), U5.9 (4A), U5.10 (4B), U7.7 (GPIO2), U24.1; also elsewhere on the board
~ABUS_OE: U7.37 (SPICLK_P); also elsewhere on the board
~C64_RESET: R70.2, U7.42 (GPIO37); also elsewhere on the board
~FPGA_RESET: U7.43 (GPIO38); also elsewhere on the board
~OE: U25.6; also elsewhere on the board
~mIO1: LD5.1 (K), R53.1, U7.47 (MTDI), U24.4; also elsewhere on the board
~mIO2: LD1.1 (K), R65.1, U7.48 (MTMS); also elsewhere on the board
~mRE: R59.1, U5.3 (4Y); also elsewhere on the board
~mVCS0: R36.1, U7.45 (MTDO), U24.2; also elsewhere on the board
~mWE: R60.2, U5.6 (4Y); also elsewhere on the board

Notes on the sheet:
R/W Adapter for RE and WE signals as VERA MODULE wants
/IO1 ($DE00-$DEFF) -> GeoRAM window, data driven by the ESP32 (U19 enabled by /IO1) /IO2 $DF00-$DF1F and VERA selected through $DFFD -> mVCS0 (DEV_SEL_N) active /IO2 $DFFD/$DFFE/$DFFF -> VERA select latch, GeoRAM page/block (write only)
VERA SELECT: latch $DFFD, software only
Accessing $DFXX (/IO2)
ESP32 RESET SWITCH
C64 Expansion Port Decoder: /IO1 GeoRAM window ($DE00-$DEFF), /IO2 VERA registers ($DF00-$DF1F), latch and GeoRAM registers ($DFFD-$DFFF)
Accessing $DEXX (/IO1)
HARDWARE DRIVEN LEDS
ESP32 BOOT SWITCH
C64 RESET IS ALWAYS ASSERTED WHEN POWERING UP THE MEMORY CONTROLLER
C64 SIGNALS ARE ALWAYS NOT VALIDATED WHEN POWERING UP THE MEMORY CONTROLLER AND THE SYSTEM CORE

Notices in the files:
README.md:
This project is licensed under the **GNU General Public License v3.0**.
├── 📄 LICENSE # Licenza GPL v3
Questo progetto è licenziato sotto la **GNU General Public License v3.0**.
